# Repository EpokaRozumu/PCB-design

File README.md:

Projekt studencki polegający na zaprojektowaniu płytki PCB na podstawie danego schematu.
Generator dźwięku oparty na układzie NE555

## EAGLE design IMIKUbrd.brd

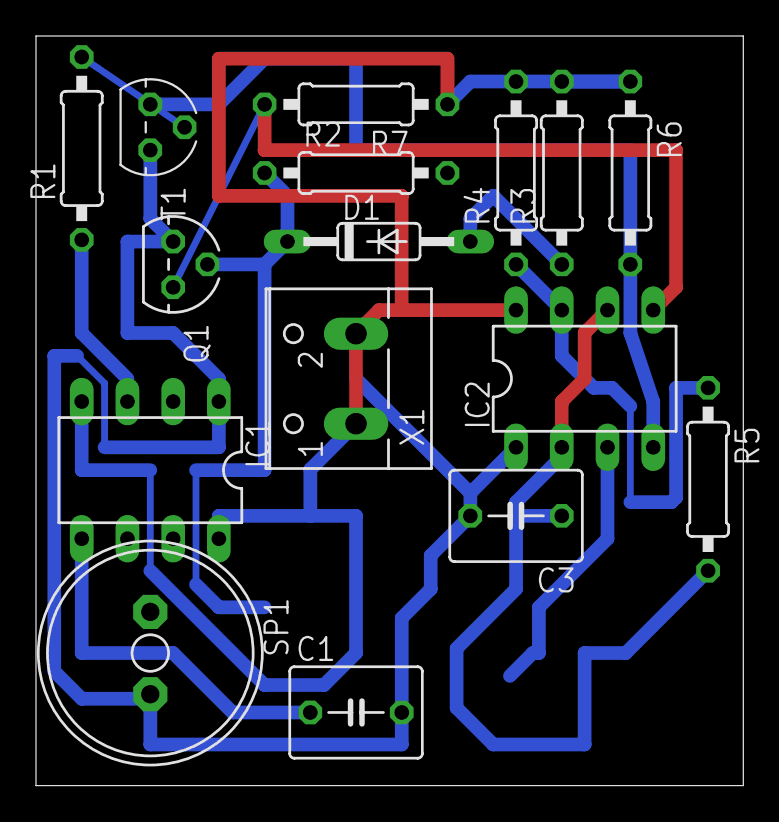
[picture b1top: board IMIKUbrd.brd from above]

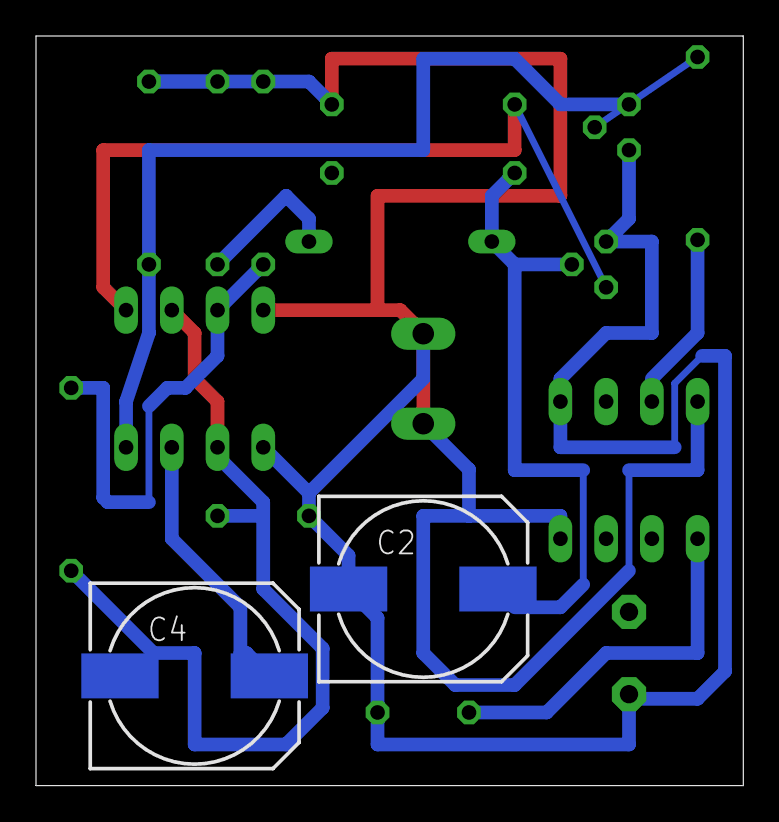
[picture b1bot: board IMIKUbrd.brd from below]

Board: 2 copper layers, 39.3 x 41.6 mm, 18 parts (2 on the bottom side), 11 nets.

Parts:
C1: 100nF; C050-050X075
C2: 470uF; 140CLH-1014
C3: 330nF; C050-050X075
C4: 220uF; 140CLH-1014
D1: 1N4148DO35-10; DO35-10
IC1, IC2: NE555; DIL-08
Q1: BC557; TO92
R1: 10k; 0207/10
R2, R5, R6, R7: 1k; 0207/10
R3: 6k8; 0207/10
R4: 5k6; 0207/10
SP1: AL11P
T1: BC547; TO92
X1: W237-102

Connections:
+5V: IC1.4, IC1.8, IC2.8, R3.2, R4.2, R6.1, R7.1, X1.1
GND: C1.2, C2.-, C3.2, IC1.1, IC2.1, Q1.3, SP1.+, T1.1, X1.2
unnamed: D1.A, R3.1
unnamed: C2.+, D1.C, Q1.2, R2.1
unnamed: R1.2, T1.2
unnamed: C4.+, IC2.3
unnamed: C3.1, IC2.2, IC2.6
unnamed: IC2.7, R4.1, R5.1
unnamed: C1.1, IC1.5
unnamed: IC2.4, R6.2, T1.3
unnamed: IC2.5, Q1.1, R7.2
